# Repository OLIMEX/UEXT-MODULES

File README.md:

# UEXT-MODULES
OSHW UEXT modules

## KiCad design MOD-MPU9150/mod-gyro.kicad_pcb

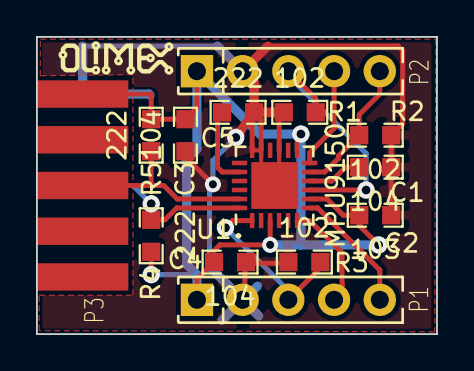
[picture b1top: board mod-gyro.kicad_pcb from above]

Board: 2 copper layers, 22.2 x 16.5 mm, 14 parts (0 on the bottom side), 12 nets.

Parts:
C1, C3, C4: 104; C_0603
C2: 103; C_0603
C5: 222; C_0603
P1, P2: CONN_01X05; SIP5_Housing
P3: HE10-10; UEXTF
R1, R2, R3: 102; R_0603
R4, R5: 222; R_0603
U1: MPU9150; QFN-24-1EP_4x4mm_Pitch0.5mm

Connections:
/SCL: P3.5, R5.2, U1.23
/SDA: P3.6, R4.2, U1.24
AD0: P2.3, R1.1, U1.9
CLKIN: P1.3, R3.1, U1.1
GND: C1.2, C2.2, C3.2, C4.2, C5.1, P1.2, P2.2, P3.2, R1.2, R2.2, R3.2, U1.15, U1.17, U1.18, U1.25
unnamed: C1.1, U1.10
unnamed: C5.2, U1.20
unnamed: P1.4, U1.6
unnamed: P1.5, U1.7
unnamed: P2.4, U1.12
unnamed: P2.5, R2.1, U1.11
VDD: C2.1, C3.1, C4.1, P1.1, P2.1, P3.1, R4.1, R5.1, U1.3, U1.8, U1.13

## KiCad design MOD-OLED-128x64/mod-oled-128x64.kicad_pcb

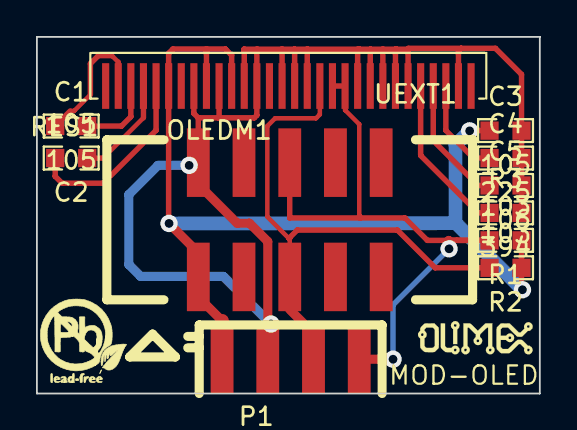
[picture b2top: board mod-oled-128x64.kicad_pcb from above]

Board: 2 copper layers, 27.9 x 19.8 mm, 12 parts (0 on the bottom side), 11 nets.

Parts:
C1, C2, C3: 105; C_0603
C4: 225; C_0603
C5: 106; C_0603
OLEDM1: IROP055; IROP055-SSD1306Z-PADS-ONLY
P1: CONN_01X04; SIP4_SMD
R1, R2: 103; R_0603
R3: 394; R_0603
RES1: CONN_01X01; TP
UEXT1: CONN_02X05; UEXTM-SMD

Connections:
/SCL: OLEDM1.18, P1.3, R2.2, UEXT1.5
/SDA: OLEDM1.19, OLEDM1.20, P1.4, R1.2, UEXT1.6
/VDD: C3.1, OLEDM1.6, OLEDM1.9, OLEDM1.11, P1.1, R1.1, R2.1, UEXT1.1
GND: C3.2, C4.2, C5.2, OLEDM1.8, OLEDM1.10, OLEDM1.12, OLEDM1.13, OLEDM1.15, OLEDM1.16, OLEDM1.17, OLEDM1.21, OLEDM1.22, OLEDM1.23, OLEDM1.24, OLEDM1.25, OLEDM1.29, P1.2, R3.2, UEXT1.2
unnamed: C1.1, OLEDM1.2
unnamed: C1.2, OLEDM1.3
unnamed: C2.1, OLEDM1.4
unnamed: C2.2, OLEDM1.5
unnamed: C4.1, OLEDM1.28
unnamed: C5.1, OLEDM1.27
unnamed: OLEDM1.26, R3.1

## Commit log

2015-03-12 MOD-MPU9150 and MOD-OLED-128x64
2015-05-28 MOD-LCD3310 files and examples
2015-05-28 Updated few examples
2015-05-28 Example updates
2015-05-29 Updated few of the files
2015-07-03 Added more modules and examples
2018-10-29 Add MOD-IO2 resources, exactly from Olimex product page
2018-10-29 Add product image from product page
2018-10-29 Fix image path
2018-10-29 Improve subsection aesthetic
2018-12-03 adc0 read corrected
2021-10-05 lcd3310: clarify and simplify pin changes
    For the ESP-PoE-ISO I had to change the pin numberings.
    They were originally as follows, but it was unclear what hardware they were for.
    MOSI=16
    SCK=15
    CS=13
    RES=3
